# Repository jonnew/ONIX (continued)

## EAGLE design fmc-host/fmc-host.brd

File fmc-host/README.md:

:warning: This headstage has moved to a dedicated repository: https://github.com/open-ephys/onix-fmc-host.
This folder should be considered archived.

# FMC Host Board
This card serves as host interface for serialized headstages and miniscopes, as
well as general purpose analog and digital IO. This board is a VITA-57.1
compliant module that uses high pin-count FMC connector. In combination with a
base FPGA board (e.g. [Numato Lab
Nereid](https://numato.com/product/nereid-kintex-7-pci-express-fpga-development-board),
it provides host PC communication for the following:

- Two deserailizers for any multifunction headstage conforming to our
  serialization protocol
- 12x 16-bit, +/-10V analog outputs or inputs. Direction selected via analog
  switch controllable over the FMC connector. Analog inputs are separated into
  2 simultaneously sampled 6-channel banks. When analog outputs are used, they
  are are always looped back using the analog inputs.
- 3x high speed LVDS input pairs
- 2x high speed LVDS outputs pairs
- 2x high speed, arbitrary logic-level, singled-ended lock inputs
- 1x high speed single ended, 50 ohm clock output
- 4x MLVDS input or output trigger lines

Easy access to IO is provided by the [breakout board](../breakout/README.md).

## Gerber Files
{% include gerber_layers.md %}

## Bill of Materials
The bill of materials for this device can be found
[here](https://docs.google.com/spreadsheets/d/1F-KWcdvH_63iXjZf0cgCfDiFX6XXW3qw6rlR8DZrFpQ/edit#gid=1976092058).

## Manufacturing Requirements
In order to meet approximately correct trace impedances, the design assumes the following stackup:

1. Top Copper 0.035 mm
1. Prepreg (2313\*1) 0.1 mm
1. Inner Copper 0.0175 mm
1. Core (Copper) 0.565 mm
1. Inner Copper 0.0175 mm
1. Prepeg (2116\*1) 0.127 mm
1. Inner Copper 0.0175 mm
1. Core (Copper) 0.565 mm
1. Inner Copper 0.0175 mm
1. Prepreg (2313\*1) 0.1 mm
1. Bottom Copper 0.0175 mm

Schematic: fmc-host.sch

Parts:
C1, C2, C6, C7, C27, C28, C35, C36, C37, C38, C72, C73, C74, C75, C81, C82, C83, C93, C94, C108, C120, C139, C140: 10uF; 1206
C3, C4, C8, C9, C10, C11, C14, C15, C16, C17, C18, C19, C20, C23, C24, C31, C32, C33, C34, C39, C43, C45, C46, C47, C48, C49, C50, C51, C54, C55, C56, C57, C58, C62, C63, C65, C67, C69, C70, C80, C85, C86, C87, C88, C89, C91, C92, C95, C101, C102, C106, C109, C112, C113, C114, C116, C117, C133, C134, C135, C137, C138: 0.1uF; 0402
C5, C29, C30: 4.7nF; 0402
C12, C13, C21, C22, C25, C26, C52, C53, C59, C60, C84, C124, C125, C126: 10nF; 0402
C40, C41: 47nF; 0402
C42, C44, C66, C68, C76, C77, C78, C90: 1uF; 0805
C61, C64, C71, C79, C97, C98, C103, C105, C107, C110, C111, C115, C118, C119, C121, C122, C123, C127, C128, C129: 10uF; 0805
C96, C99, C100, C104, C130, C131, C132, C136: 47uF; 1210
D1, D2, D3: HSMG-C280; LED-0402
D4, D5: SESD0402X1UN-0020-090; 0402P-DFN
D6, D7, D8: BAR66; SOT23
D9: KDZ4.3B; SOD123
D10, D11: APFA3011-AK13/F; RGB_LED_SMD-6
F1, F2, F3: C014F-2; 1812
J1, J2, J3, J4, J5: SMA002; MMCX-THRU
J6: ESHF-105-01-L-D-SM-K-TR
J7: 12226-8250-00FR; 12226-82X0-00XX
J8: 95278-101A16LF; JP2X8_SMD
J9: FMC_SINGLE_WIDTH_MODULE
J10: ASP-134488-01; FMC_HPC_MALE
L1, L2: 1008PS-472; 1008PS
L3, L4, L9, L10, L11, L12: BLM18KG601SN1D; 0603
L5, L6: SRNxx-101M; SRN6045TA
L7, L8: MPZ2012S102AT000; 0805
L13: L_1210; 1210
L14, L15, L16, L17, L18, L19: BLM15PX601SN1D; 0402; PARTNO BLM15PX601SN1D
Q1, Q2: SI1012R; SC75
R1, R6, R7, R12, R13, R63, R64: 2k; 0402
R2, R3, R36, R37, R38, R39, R46, R49, R77, R79, R81: 4.7k; 0402
R4, R5, R33, R44, R45: 3k; 0402
R8, R9, R10, R11, R14, R15: 150,0.25W; 0603
R16, R17, R55, R56, R57, R58, R82: 165k; 0402
R18, R19, R41, R43, R65, R70, R71, R72, R73, R74, R84, R85: 10k; 0402
R20, R21, R47, R48, R50, R51, R52, R53: 1k; 0402
R22, R24: 5.6k 1%; 0402
R23, R25: 21k 1%; 0402
R26, R27: 60 1%; 0402
R28, R29, R34, R35: 49.9; 0402
R30, R31, R32: 100; 0402
R40, R42: DNP; 0402
R54, R69: 0; 0402
R59, R60, R61, R62: 2.2k; RN2X8-1506
R66, R67: 3.48k; 0402
R68: 649k; 0402
R75: 2.2k; 0402
R76: 15k; 0402
R78, R80: 43k; 0402
R83: 178k; 0402
R86, R87: 73.2k; 0402
S1, S2: CHS-01TA; DIP01-SMD-GULL
S3: CHS-02TB
SJ1, SJ2: SJ2_0201; SJ_2_0201
TP1, TP2, TP4, TP5, TP6, TP7, TP11, TP12, TP13, TP14, TP15, TP16: TPB1,27; B1,27
TP3, TP8, TP9, TP10, TP17, TP18: TPB2,54; B2,54
U1: SN74LVC2G34DCKR; SC70
U2: SN65LVDS9638DGN; MSOP-8-PAD-3X3
U3: FIN1032MTCX; TSSOP-16
U4: LTC2875_DFN; DFN83X3
U5, U6: ADCMP600; SOT-23-5
U7, U8, U9: DG1412E; QFN16-4X4MM
U10, U11: DS90UB934-Q1; WQFN48-7X7-PAD
U12: DS91M040; WQFN32-5X5
U13: AD5766BCPZ-RL7; CP_40_7
U14: MCP47FEB02A0-E/ST; TSSOP-8
U15: LM4132AMF-2.5/NOPBCT-ND; SOT-23-5
U16: AD7617BSTZ; ST_80_2
U17: AD5142BCPZ10; CP_16_27-L
U18: LTM4622A; BGA_5X5_625X625
U19: TPS62293DRV; WSON6-2X2
U20, U21: TPS7A49; PVSON-N8+4-3X3
U22: TPS7A30; PVSON-N8+4-3X3
U23: 24AA64ST; TSSOP8
U24: LTM8049_BGA; LTM8049
X2, X3: OE-LOGO_7X5; OE-LOGO-7X5

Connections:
!ADC_CS: J10.H13 (LA07_P), U16.63 (!CS)
!ADC_RESET: J10.F10 (HA08_P), R72.2
!DAC_CS: J10.J16 (HA14_N), U13.8 (!CS)
!DAC_RESET: J10.F14 (HA12_N), U13.3 (!RESET)
!LINK_PWR_ADJ_CS: J10.F38 (HB20_N), U17.14 (!CS)
!LINK_PWR_ADJ_RESET: J10.E37 (HB21_N), U17.16 (!RESET)
$N1: D8.3 (COMM), F2.2, R5.2, R9.2, R11.2, R15.2, R29.1
$N2: D6.3 (COMM), F3.2, U1.4 (OUT2), U1.6 (OUT1)
$N3: D7.3 (COMM), F1.2, R4.2, R8.2, R10.2, R14.2, R28.1
+1V8: C88.2, C89.2, C93.2, C94.2, C108.2, L3.2, L4.2, L9.1, L10.1, L13.1, R22.1, R24.1, R40.1, R42.1, TP16.TP, U10.17 (VDD18), U11.17 (VDD18), U19.3 (FB)
+3V3: C11.2, C23.1, C24.1, C29.1, C30.1, C33.1, C34.1, C39.1, C76.2, C80.2, C84.2, C91.2, C95.2, C98.2, C113.2, C115.2, C116.2, C119.2, C120.2, C136.2, C137.2, C138.2, C139.1, C140.1, J10.E39 (VADJ), J10.F40 (VADJ), J10.G39 (VADJ), J10.H40 (VADJ), J10.J39 (VIO_B_M2C), J10.K40 (VIO_B_M2C), L11.1, L12.1, R36.2, R37.2, R38.2, R39.2, R46.2, R49.2, R63.2, R64.2, R69.1, R70.1, R71.1, R75.1, R84.2, R85.2, S1.2, S2.2, TP11.TP, U1.5 (VCC), U2.1 (VCC), U3.4 (EN), U3.16 (VCC), U4.3 (VCC), U5.5 (V+), U6.5 (V+), U10.4 (OSS_SEL), U10.5 (OEN), U11.4 (OSS_SEL), U11.5 (OEN), U12.11 (VDD), U12.12 (VDD), U12.29 (VDD), U12.30 (VDD), U13.4 (VLOGIC), U14.1 (VDD), U14.2 (REFA), U16.49 (VDRIVE), U17.9 (VDD), U17.10 (VLOGIC), U17.15 (INDEP), U19.2 (MODE), U19.4 (EN), U19.5 (VIN), U24.A5 (VIN1), U24.A6 (VIN1), U24.A7 (VIN1), U24.B7 (RUN1), U24.K7 (RUN2), U24.L5 (VIN2), U24.L6 (VIN2), U24.L7 (VIN2)
+5V_AN: C61.2, C64.2, C71.2, C79.2, C83.1, C85.2, C86.2, C87.2, C92.2, C109.2, C110.2, L14.1, R1.2, TP1.TP, U13.28 (AVCC), U15.3 (EN), U15.4 (VIN), U16.6 (VCC), U16.15 (VCC), U16.30 (VCC), U16.71 (VCC)
+12V: C118.2, C130.2, C133.2, C134.2, J7.1, J7.26, J10.C35 (12P0V1), J10.C37 (12P0V2), R44.2, R45.2, TP12.TP, U18.A2 (VIN), U18.B3 (VIN), U18.D3 (VIN), U18.E2 (VIN)
+13V_AN: C8.2, C9.2, C10.2, C106.2, C107.2, L15.1, R2.2, TP2.TP, U7.11 (V+), U8.11 (V+), U9.11 (V+), U13.26 (AVDD)
+15V: C131.2, L17.2, L18.2, R82.1, U24.A1 (VOUT1P), U24.A2 (VOUT1P), U24.B1 (VOUT1P), U24.B2 (VOUT1P)
-13V_AN: C18.2, C19.2, C20.2, C101.2, C105.2, L16.1, R3.2, TP4.TP, U7.2 (V-), U7.PAD (V-), U8.2 (V-), U8.PAD (V-), U9.2 (V-), U9.PAD (V-), U13.6 (AVSS), U13.PAD (AVSS)
-15V: C132.1, L19.2, R83.1, U24.G1 (VOUT2N), U24.G2 (VOUT2N), U24.H1 (VOUT2N), U24.H2 (VOUT2N), U24.J2 (VOUT2N)
ADC_BUSY: J10.J12 (HA11_P), U16.67 (BUSY)
ADC_CONVST: J10.K13 (HA10_P), U16.68 (CONVST)
ADC_MISO_A: J10.K11 (HA06_N), U16.57 (DB12/SDOA)
ADC_MISO_B: J10.J10 (HA07_N), U16.56 (DB11/SDOB)
ADC_MOSI: J10.K10 (HA06_P), U16.55 (DB10/SDI)
ADC_SCLK: J10.J13 (HA11_N), U16.62 (SCLK/!RD)
ADDR0: J10.C27 (LA27_N), R84.1, S3.4
ADDR1: J10.C26 (LA27_P), R85.1, S3.3
AGND: C8.1, C9.1, C10.1, C18.1, C19.1, C20.1, C61.1, C64.1, C71.1, C79.1, C83.2, C85.1, C86.1, C87.1, C90.1, C92.1, C97.1, C101.1, C102.1, C103.1, C105.1, C106.1, C107.1, C109.1, C110.1, D1.C, D2.C, D3.A, J7.13, J7.14, R54.1, R59.C2, R59.C4, R59.C6, R59.C7, R60.C1, R60.C3, R60.C5, R60.C6, R60.C7, R60.C8, R61.C2, R61.C3, R61.C5, R61.C7, R62.C1, R62.C2, R62.C3, R62.C4, R62.C6, R62.C8, TP3.TP, U7.3 (GND), U8.3 (GND), U9.3 (GND), U13.10 (AGND), U13.20 (NIC), U13.23 (N0), U13.24 (N1), U13.25 (NIC), U13.29 (AGND), U13.31 (NIC), U15.2 (GND), U16.5 (AGND), U16.16 (AGND), U16.29 (AGND), U16.32 (REFGND), U16.34 (REFINOUTGND), U16.69 (REGGND), U16.72 (AGND)
AIN_AOUT0: J10.F11 (HA08_N), U9.15 (IN1)
AIN_AOUT1: J10.D11 (LA05_P), U9.6 (IN4)
AIN_AOUT2: J10.E12 (HA13_P), U9.7 (IN3)
AIN_AOUT3: J10.H10 (LA04_P), U9.14 (IN2)
AIN_AOUT4: J10.E18 (HA20_P), U8.15 (IN1)
AIN_AOUT5: J10.J9 (HA07_P), U8.6 (IN4)
AIN_AOUT6: J10.G10 (LA03_N), U8.7 (IN3)
AIN_AOUT7: J10.F17 (HA15_N), U8.14 (IN2)
AIN_AOUT8: J10.H20 (LA15_N), U7.7 (IN3)
AIN_AOUT9: J10.J18 (HA18_P), U7.14 (IN2)
AIN_AOUT10: J10.G19 (LA16_N), U7.6 (IN4)
AIN_AOUT11: J10.H19 (LA15_P), U7.15 (IN1)
AIO_0: J7.7, R59.C1, U9.16 (D1)
AIO_1: J7.20, R59.C3, U9.5 (D4)
AIO_2: J7.8, R59.C5, U9.8 (D3)
AIO_3: J7.21, R59.C8, U9.13 (D2)
AIO_4: J7.9, R60.C4, U8.16 (D1)
AIO_5: J7.22, R60.C2, U8.5 (D4)
AIO_6: J7.10, R62.C5, U8.8 (D3)
AIO_7: J7.23, R62.C7, U8.13 (D2)
AIO_8: J7.11, R61.C6, U7.8 (D3)
AIO_9: J7.24, R61.C8, U7.13 (D2)
AIO_10: J7.12, R61.C4, U7.5 (D4)
AIO_11: J7.25, R61.C1, U7.16 (D1)
AOUT0: U7.1 (S1), U13.32 (VOUT0)
AOUT1: U7.4 (S4), U13.33 (VOUT1)
AOUT2: U7.9 (S3), U13.34 (VOUT2)
AOUT3: U7.12 (S2), U13.35 (VOUT3)
AOUT4: U8.1 (S1), U13.36 (VOUT4)
AOUT5: U8.4 (S4), U13.37 (VOUT5)
AOUT6: U8.12 (S2), U13.38 (VOUT6)
AOUT7: U8.9 (S3), U13.39 (VOUT7)
AOUT8: U9.9 (S3), U13.12 (VOUT8)
AOUT9: U9.12 (S2), U13.13 (VOUT9)
AOUT10: U9.4 (S4), U13.14 (VOUT10)
AOUT11: U9.1 (S1), U13.15 (VOUT11)
CAN_N: R27.2, SJ1.2, U4.6 (CANL)
CAN_P: R26.2, SJ2.2, U4.7 (CANH)
CAN_RX: J10.K8 (HA02_N), U4.4 (RXD)
CAN_TX: J10.K7 (HA02_P), U4.1 (TXD)
CLKIN0: J10.D21 (LA17_N_CC), TP7.TP, U5.1 (OUT)
CLKIN1: J10.E19 (HA20_N), TP6.TP, U6.1 (OUT)
CLKIN_TERM0: J10.K19 (HA21_P), R20.1
CLKIN_TERM1: J10.K17 (HA17_N_CC), R21.1
CLKIN_VBIAS_SCL: J10.J21 (HA22_P), R64.1, U14.7 (SCL)
CLKIN_VBIAS_SDA: J10.K20 (HA21_N), R63.1, U14.8 (SDA)
CLKOUT: J10.D20 (LA17_P_CC), U1.1 (IN3), U1.3 (IN2)
DAC_MISO: J10.K16 (HA17_P_CC), U13.9 (MISO)
DAC_MOSI: J10.H14 (LA07_N), U13.5 (MOSI)
DAC_MUX: TP15.TP, U13.27 (MUX_OUT)
DAC_SCLK: J10.J15 (HA14_P), U13.7 (SCLK)
DEBUG0: J8.2, J10.C10 (LA06_P)
DEBUG1: J8.4, J10.C11 (LA06_N)
DEBUG2: J8.6, J10.D14 (LA09_P)
DEBUG3: J8.8, J10.C14 (LA10_P)
DEBUG4: J8.10, J10.D15 (LA09_N)
DEBUG5: J8.12, J10.C15 (LA10_N)
DEBUG6: J8.14, J10.C18 (LA14_P)
DEBUG7: J8.16, J10.C19 (LA14_N)
DES_A_D0: J10.F34 (HB16_P), U11.24 (ROUT0)
DES_A_D1: J10.K35 (HB14_N), U11.23 (ROUT1)
DES_A_D2: J10.J34 (HB15_N), U11.22 (ROUT2)
DES_A_D3: J10.K34 (HB14_P), U11.21 (ROUT3)
DES_A_D4: J10.E33 (HB19_P), U11.19 (ROUT4)
DES_A_D5: J10.J33 (HB15_P), U11.18 (ROUT5)
DES_A_D6: J10.F32 (HB12_N), U11.16 (ROUT6)
DES_A_D7: J10.E31 (HB13_N), U11.15 (ROUT7)
DES_A_D8: J10.K32 (HB10_N), U11.14 (ROUT8)
DES_A_D9: J10.F31 (HB12_P), U11.13 (ROUT9)
DES_A_D10: J10.J31 (HB11_N), U11.12 (ROUT10)
DES_A_D11: J10.K31 (HB10_P), U11.11 (ROUT11)
DES_A_GPIO0: J10.J37 (HB18_N), U11.28 (GPIO0)
DES_A_GPIO1: J10.K37 (HB17_P_CC), U11.27 (GPIO1)
DES_A_GPIO2: J10.J36 (HB18_P), U11.26 (GPIO2)
DES_A_GPIO3: J10.E34 (HB19_N), R49.1, U11.25 (GPIO3/INTB)
DES_A_HSYNC: J10.E30 (HB13_P), U11.10 (HSYNC)
DES_A_LEDG: J10.F28 (HB08_P), R53.2
DES_A_LOCK: J10.E27 (HB09_P), R48.2, R56.2, U11.48 (LOCK)
DES_A_PASS: J10.J28 (HB07_N), R51.2, R58.2, U11.47 (PASS)
DES_A_PCLK: J10.K28 (HB06_P_CC), U11.8 (PCLK)
DES_A_PDB: J10.F35 (HB16_N), U11.30 (PDB)
DES_A_SCL: J10.F29 (HB08_N), R37.1, U11.2 (SCL)
DES_A_SDA\: J10.E28 (HB09_N), R39.1, U11.1 (SDA)
DES_A_VSYNC: J10.J30 (HB11_P), U11.9 (VSYNC)
DES_B_D0: J10.H29 (LA24_N), U10.24 (ROUT0)
DES_B_D1: J10.H28 (LA24_P), U10.23 (ROUT1)
DES_B_D2: J10.G28 (LA25_N), U10.22 (ROUT2)
DES_B_D3: J10.G27 (LA25_P), U10.21 (ROUT3)
DES_B_D4: J10.D27 (LA26_N), U10.19 (ROUT4)
DES_B_D5: J10.D26 (LA26_P), U10.18 (ROUT5)
DES_B_D6: J10.H26 (LA21_N), U10.16 (ROUT6)
DES_B_D7: J10.G25 (LA22_N), U10.15 (ROUT7)
DES_B_D8: J10.H25 (LA21_P), U10.14 (ROUT8)
DES_B_D9: J10.D24 (LA23_N), U10.13 (ROUT9)
DES_B_D10: J10.G24 (LA22_P), U10.12 (ROUT10)
DES_B_D11: J10.D23 (LA23_P), U10.11 (ROUT11)
DES_B_GPIO0: J10.H32 (LA28_N), U10.28 (GPIO0)
DES_B_GPIO1: J10.G31 (LA29_N), U10.27 (GPIO1)
DES_B_GPIO2: J10.H31 (LA28_P), U10.26 (GPIO2)
DES_B_GPIO3: J10.G30 (LA29_P), R46.1, U10.25 (GPIO3/INTB)
DES_B_HSYNC\: J10.H23 (LA19_N), U10.10 (HSYNC)
DES_B_LEDG: J10.G21 (LA20_P), R52.2
DES_B_LOCK: J10.J22 (HA22_N), R47.2, R55.2, U10.48 (LOCK)
DES_B_PASS: J10.K22 (HA23_P), R50.2, R57.2, U10.47 (PASS)
DES_B_PCLK: J10.C22 (LA18_P_CC), U10.8 (PCLK)
DES_B_PDB: J10.G33 (LA31_P), U10.30 (PDB)
DES_B_SCL: J10.G22 (LA20_N), R36.1, U10.2 (SCL)
DES_B_SDA: J10.H22 (LA19_P), R38.1, U10.1 (SDA)
DES_B_VSYNC: J10.K23 (HA23_N), U10.9 (VSYNC)
DI_VBIAS0: R18.1, U14.3 (VOUT0)
DI_VBIAS1: R19.1, U14.4 (VOUT1)
DOUTP_F_A: C47.2, D5.C, J2.SIG (1), L2.2, R7.2
DOUTP_F_B: C46.2, D4.C, J1.SIG (1), L1.2, R6.2
GND: C1.1, C2.1, C3.1, C4.1, C5.2, C6.1, C7.1, C11.1, C12.1, C13.1, C14.2, C15.2, C16.2, C17.2, C21.1, C22.1, C23.2, C24.2, C25.1, C26.1, C27.1, C28.1, C29.2, C30.2, C31.2, C32.2, C33.2, C34.2, C35.1, C36.1, C37.1, C38.1, C39.2, C42.1, C43.1, C44.1, C45.1, C48.1, C49.1, C50.1, C51.1, C52.1, C53.1, C54.1, C55.1, C56.1, C57.1, C58.1, C59.1, C60.1, C62.1, C63.1, C65.1, C66.1, C67.1, C68.1, C69.1, C70.1, C72.1, C73.1, C74.1, C75.1, C76.1, C77.1, C78.1, C80.1, C81.1, C82.1, C84.1, C88.1, C89.1, C91.1, C93.1, C94.1, C95.1, C96.1, C98.1, C99.1, C100.1, C104.1, C108.1, C111.1, C112.1, C113.1, C114.1, C115.1, C116.1, C117.2, C118.1, C119.1, C120.1, C121.1, C122.1, C123.1, C124.2, C125.2, C126.2, C127.1, C128.1, C129.1, C130.1, C131.1, C132.2, C133.1, C134.1, C135.1, C136.1, C137.1, C138.1, C139.2, C140.2, D4.A, D5.A, D6.1 (A), D7.1 (A), D8.1 (A), D9.A, D10.3 (C), D10.5 (C), D10.6 (C), D11.3 (C), D11.5 (C), D11.6 (C), J1.GND@1 (2), J1.GND@2 (2), J1.GND@3 (2), J1.GND@4 (2), J2.GND@1 (2), J2.GND@2 (2), J2.GND@3 (2), J2.GND@4 (2), J3.GND@1 (2), J3.GND@2 (2), J3.GND@3 (2), J3.GND@4 (2), J4.GND@1 (2), J4.GND@2 (2), J4.GND@3 (2), J4.GND@4 (2), J5.GND@1 (2), J5.GND@2 (2), J5.GND@3 (2), J5.GND@4 (2), J7.PAD1, J7.PAD2, J8.1, J8.3, J8.5, J8.7, J8.9, J8.11, J8.13, J8.15, J10.A1 (GND), J10.A4 (GND), J10.A5 (GND), J10.A8 (GND), J10.A9 (GND), J10.A12 (GND), J10.A13 (GND), J10.A16 (GND), J10.A17 (GND), J10.A20 (GND), J10.A21 (GND), J10.A24 (GND), J10.A25 (GND), J10.A28 (GND), J10.A29 (GND), J10.A32 (GND), J10.A33 (GND), J10.A36 (GND), J10.A37 (GND), J10.A40 (GND), J10.B2 (GND), J10.B3 (GND), J10.B6 (GND), J10.B7 (GND), J10.B10 (GND), J10.B11 (GND), J10.B14 (GND), J10.B15 (GND), J10.B18 (GND), J10.B19 (GND), J10.B22 (GND), J10.B23 (GND), J10.B26 (GND), J10.B27 (GND), J10.B30 (GND), J10.B31 (GND), J10.B34 (GND), J10.B35 (GND), J10.B38 (GND), J10.B39 (GND), J10.C1 (GND), J10.C4 (GND), J10.C5 (GND), J10.C8 (GND), J10.C9 (GND), J10.C12 (GND), J10.C13 (GND), J10.C16 (GND), J10.C17 (GND), J10.C20 (GND), J10.C21 (GND), J10.C24 (GND), J10.C25 (GND), J10.C28 (GND), J10.C29 (GND), J10.C32 (GND), J10.C33 (GND), J10.C34 (GA0), J10.C36 (GND), J10.C38 (GND), J10.C40 (GND), J10.D2 (GND), J10.D3 (GND), J10.D6 (GND), J10.D7 (GND), J10.D10 (GND), J10.D13 (GND), J10.D16 (GND), J10.D19 (GND), J10.D22 (GND), J10.D25 (GND), J10.D28 (GND), J10.D35 (GA1), J10.D37 (GND), J10.D39 (GND), J10.E1 (GND), J10.E4 (GND), J10.E5 (GND), J10.E8 (GND), J10.E11 (GND), J10.E14 (GND), J10.E17 (GND), J10.E20 (GND), J10.E23 (GND), J10.E26 (GND), J10.E29 (GND), J10.E32 (GND), J10.E35 (GND), J10.E38 (GND), J10.E40 (GND), J10.F2 (GND), J10.F3 (GND), J10.F6 (GND), J10.F9 (GND), J10.F12 (GND), J10.F15 (GND), J10.F18 (GND), J10.F21 (GND), J10.F24 (GND), J10.F27 (GND), J10.F30 (GND), J10.F33 (GND), J10.F36 (GND), J10.F39 (GND), J10.G1 (GND), J10.G4 (GND), J10.G5 (GND), J10.G8 (GND), J10.G11 (GND), J10.G14 (GND), J10.G17 (GND), J10.G20 (GND), J10.G23 (GND), J10.G26 (GND), J10.G29 (GND), J10.G32 (GND), J10.G35 (GND), J10.G38 (GND), J10.G40 (GND), J10.H3 (GND), J10.H6 (GND), J10.H9 (GND), J10.H12 (GND), J10.H15 (GND), J10.H18 (GND), J10.H21 (GND), J10.H24 (GND), J10.H27 (GND), J10.H30 (GND), J10.H33 (GND), J10.H36 (GND), J10.H39 (GND), J10.J1 (GND), J10.J4 (GND), J10.J5 (GND), J10.J8 (GND), J10.J11 (GND), J10.J14 (GND), J10.J17 (GND), J10.J20 (GND), J10.J23 (GND), J10.J26 (GND), J10.J29 (GND), J10.J32 (GND), J10.J35 (GND), J10.J38 (GND), J10.J40 (GND), J10.K2 (GND), J10.K3 (GND), J10.K6 (GND), J10.K9 (GND), J10.K12 (GND), J10.K15 (GND), J10.K18 (GND), J10.K21 (GND), J10.K24 (GND), J10.K27 (GND), J10.K30 (GND), J10.K33 (GND), J10.K36 (GND), J10.K39 (GND), Q1.2 (S), Q2.2 (S), R4.1, R5.1, R16.1, R17.1, R23.2, R25.2, R33.1, R34.2, R35.2, R41.2, R43.2, R54.2, R55.1, R56.1, R57.1, R58.1, R68.2, R73.2, R74.2, R77.1, R79.1, R81.1, R86.2, R87.2, S3.1, S3.2, TP8.TP, TP9.TP, TP10.TP, TP17.TP, TP18.TP, U1.2 (GND), U2.4 (GND), U2.PAD (GND), U3.8 (GND), U3.12 (!EN), U4.2 (GND), U4.PAD (GND), U5.2 (V-), U6.2 (V-), U10.43 (RES1), U10.44 (RES2), U10.46 (SEL), U10.PAD (GND), U11.43 (RES1), U11.44 (RES2), U11.46 (SEL), U11.PAD (GND), U12.31 (GND), U12.PAD (GND), U13.2 (DGND), U14.5 (AVSS), U14.6 (LAT/HVC), U16.37 (SEQEN), U16.38 (HW_RNGSEL1), U16.39 (HW_RNGSEL0), U16.41 (DB0), U16.42 (DB1), U16.43 (DB2), U16.44 (DB3), U16.46 (DB5/CRCEN), U16.47 (DB6), U16.48 (DB7), U16.50 (DGND), U16.51 (REGGNDD), U16.53 (DB8), U16.54 (DB9), U16.58 (DB13/OS0), U16.59 (DB14/OS1), U16.60 (DB15/OS2), U16.61 (WR!/BURST), U16.64 (CHSEL0), U16.65 (CHSEL1), U16.66 (CHSEL2), U17.1 (GND), U17.3 (W1), U17.5 (VSS), U17.7 (W2), U17.PAD (VSS), U18.B5 (GND), U18.C1 (GND), U18.C2 (GND), U18.C5 (SYNC/MODE), U18.D5 (GND), U19.6 (GND), U19.PAD (GND), U20.3 (NC), U20.4 (GND), U20.PAD1 (PAD), U20.PAD2 (PAD), U20.PAD3 (PAD), U20.PAD4 (PAD), U20.PAD5 (PAD), U21.3 (NC), U21.4 (GND), U21.PAD1 (PAD), U21.PAD2 (PAD), U21.PAD3 (PAD), U21.PAD4 (PAD), U21.PAD5 (PAD), U22.3 (NC), U22.4 (GND), U22.PAD1 (PAD), U22.PAD2 (PAD), U22.PAD3 (PAD), U22.PAD4 (PAD), U22.PAD5 (PAD), U23.1 (A0), U23.2 (A1), U23.3 (A2), U23.4 (GND), U23.7 (WP), U24.A3 (GND), U24.A4 (GND), U24.B3 (GND), U24.B4 (GND), U24.B5 (GND), U24.B6 (GND), U24.C2 (VOUT1N), U24.C3 (GND), U24.C4 (GND), U24.C5 (GND), U24.C6 (GND), U24.D1 (VOUT1N), U24.D2 (VOUT1N), U24.D3 (GND), U24.D4 (GND), U24.D5 (GND), U24.D7 (SYNC1), U24.E1 (VOUT1N), U24.E2 (VOUT1N), U24.E3 (GND), U24.E4 (GND), U24.E5 (GND), U24.F1 (GND), U24.F2 (GND), U24.F5 (GND), U24.F6 (GND), U24.F7 (GND), U24.G3 (GND), U24.G4 (GND), U24.G5 (GND), U24.H3 (GND), U24.H4 (GND), U24.H5 (GND), U24.J3 (GND), U24.J4 (GND), U24.J5 (GND), U24.J6 (GND), U24.K1 (VOUT2P), U24.K2 (VOUT2P), U24.K3 (GND), U24.K4 (GND), U24.K5 (GND), U24.K6 (GND), U24.L1 (VOUT2P), U24.L2 (VOUT2P), U24.L3 (GND), U24.L4 (GND)
LINK_A_PWR_EN: J10.H37 (LA32_P), R74.1, U18.B2 (RUN2)
LINK_B_PWR_EN: J10.K38 (HB17_N_CC), R73.1, U18.D2 (RUN1)
LINK_PWR_ADJ_MISO: J10.F37 (HB20_P), R75.2, U17.13 (MISO)
LINK_PWR_ADJ_MOSI: J10.E36 (HB21_P), U17.12 (MOSI)
LINK_PWR_ADJ_SCLK: J10.H38 (LA32_N), U17.11 (SCLK)
LVDS_DIN0: J10.J2 (CLK1_C2M_P), U3.3 (AOUT)
LVDS_DIN0_N: J7.4, R30.1, U3.1 (A-)
LVDS_DIN0_P: J7.17, R30.2, U3.2 (A+)
LVDS_DIN1: J10.H5 (CLK0_M2C_N), U3.5 (BOUT)
LVDS_DIN1_N: J7.16, R31.1, U3.7 (B-)
LVDS_DIN1_P: J7.3, R31.2, U3.6 (B+)
LVDS_DIN2: J10.H4 (CLK0_M2C_P), U3.11 (COUT)
LVDS_DIN2_N: R32.1, SJ2.1, U3.9 (C-)
LVDS_DIN2_N/CAN_P: J7.2, SJ2.COM
LVDS_DIN2_P: R32.2, SJ1.1, U3.10 (C+)
LVDS_DIN2_P/CAN_N: J7.15, SJ1.COM
LVDS_DOUT0: J10.J3 (CLK1_C2M_N), U2.2 (AIN)
LVDS_DOUT0_N: J7.19, U2.7 (AOUT-)
LVDS_DOUT0_P: J7.6, U2.8 (AOUT+)
LVDS_DOUT1: J10.K4 (CLK1_M2C_P), U2.3 (BIN)
LVDS_DOUT1_N: J7.18, U2.5 (BOUT-)
LVDS_DOUT1_P: J7.5, U2.6 (BOUT+)
MLDVS_EN: J10.H8 (LA02_N), U12.10 (MDE)
MLDVS_RO0: J10.G2 (CLK0_C2M_P), U12.1 (RO0)
MLDVS_RO1: J10.E3 (HA01_N_CC), U12.3 (RO1)
MLDVS_RO2: J10.G7 (LA00_N_CC), U12.5 (RO2)
MLDVS_RO3: J10.F4 (HA00_P_CC), U12.7 (RO3)
MLVDS_CLK_0_N: J6.9, U12.24 (B0)
MLVDS_CLK_0_P: J6.10, U12.23 (A0)
MLVDS_CLK_1_N: J6.7, U12.22 (B1)
MLVDS_CLK_1_P: J6.8, U12.21 (A1)
MLVDS_CLK_2_N: J6.3, U12.20 (B2)
MLVDS_CLK_2_P: J6.4, U12.19 (A2)
MLVDS_CLK_3_N: J6.1, U12.18 (B3)
MLVDS_CLK_3_P: J6.2, U12.17 (A3)
MLVDS_DE_!RE0: J10.F7 (HA04_P), U12.25 (DE0), U12.26 (!RE0)
MLVDS_DE_!RE1: J10.E7 (HA05_N), U12.27 (DE1), U12.28 (!RE1)
MLVDS_DE_!RE2: J10.H7 (LA02_P), U12.13 (!RE2), U12.14 (DE2)
MLVDS_DE_!RE3: J10.F8 (HA04_N), U12.15 (!RE3), U12.16 (DE3)
MLVDS_DI0: J10.G3 (CLK0_C2M_N), U12.2 (DI0)
MLVDS_DI1: J10.E2 (HA01_P_CC), U12.4 (DI1)
MLVDS_DI2: J10.G6 (LA00_P_CC), U12.6 (DI2)
MLVDS_DI3: J10.F5 (HA00_N_CC), U12.8 (DI3)
unnamed: L13.2, U19.1 (SW)
unnamed: Q1.3 (D), R8.1, R10.1, R14.1
unnamed: R28.2, U5.3 (+IN)
unnamed: L1.1, L5.2, R6.1, R12.2
unnamed: R67.1, U18.A4 (FB2)
unnamed: F2.1, J4.SIG (1)
unnamed: Q2.3 (D), R9.1, R11.1, R15.1
unnamed: C112.2, U18.A3 (TRACK/SS2)
unnamed: R87.1, U24.G7 (RT2)
unnamed: R66.1, U18.E4 (FB1)
unnamed: F1.1, J3.SIG (1)
unnamed: C114.2, U18.E3 (TRACK/SS1)
unnamed: R33.2, U4.8 (RS)
unnamed: F3.1, J5.SIG (1)
unnamed: C127.2, L17.1, U20.5 (EN), U20.8 (IN)
unnamed: D11.4 (A), R53.1
unnamed: R86.1, U24.E7 (RT1)
unnamed: C14.1, R18.2, U5.4 (-IN)
unnamed: R29.2, U6.3 (+IN)
unnamed: C15.1, R19.2, U6.4 (-IN)
unnamed: L2.1, L6.2, R7.1, R13.2
unnamed: C7.2, C17.1, L6.1, L8.2, R13.1
unnamed: R61.1, U16.79 (V3B)
unnamed: C6.2, C16.1, L5.1, L7.2, R12.1
unnamed: R83.2, U24.J1 (FBX2)
unnamed: D10.4 (A), R52.1
unnamed: C47.1, U11.41 (RIN0+)
unnamed: C41.1, U11.42 (RIN0-)
unnamed: R82.2, U24.C1 (FBX1)
unnamed: C37.2, C44.2, C49.2, U11.3 (VDD11_D)
unnamed: C38.2, C45.2, U11.20 (VDD11_DVP)
unnamed: C41.2, R35.1
unnamed: C124.1, U20.6 (NR/SS)
unnamed: Q2.1 (G), R17.2, R21.2
unnamed: U24.E6 (CLKOUT1), U24.H7 (SYNC2)
unnamed: D3.C, R3.1
unnamed: Q1.1 (G), R16.2, R20.2
unnamed: C46.1, U10.41 (RIN0+)
unnamed: R61.2, U16.80 (V3BGND)
unnamed: R76.1, R77.2, U20.2 (FB)
unnamed: C5.1, R26.1, R27.1, U4.5 (SPLIT)
unnamed: C128.2, L18.1, U21.5 (EN), U21.8 (IN)
unnamed: C125.1, U21.6 (NR/SS)
unnamed: C70.2, C78.2, C82.2, U11.34 (VDD11_FPD)
unnamed: C117.1, R72.1, U16.36 (!RESET)
unnamed: C57.2, C62.2, C66.2, C73.2, L11.2, U10.7 (VDDIO), U10.29 (VDDIO)
unnamed: C35.2, C42.2, C48.2, U10.3 (VDD11_D)
unnamed: C36.2, C43.2, U10.20 (VDD11_DVP)
unnamed: C69.2, C77.2, C81.2, U10.34 (VDD11_FPD)
unnamed: D11.1 (A), R48.1
unnamed: D11.2 (A), R51.1
unnamed: C40.1, U10.42 (RIN0-)
unnamed: R78.1, R79.2, U21.2 (FB)
unnamed: D1.A, R1.1
unnamed: C129.2, L19.1, U22.5 (EN), U22.8 (IN)
unnamed: C126.1, U22.6 (NR/SS)
unnamed: R80.1, R81.2, U22.2 (FB)
unnamed: R71.2, U16.45 (DB4/!SER1WR)
unnamed: R59.1, U16.28 (V0A)
unnamed: R70.2, U16.40 (SER/!PAR)
unnamed: C97.2, U16.31 (REFCAP)
unnamed: R59.2, U16.27 (V0AGND)
unnamed: D2.A, R2.1
unnamed: C111.2, U16.52 (REGCAPD)
unnamed: R61.8, U16.73 (V0B)
unnamed: C103.2, U16.70 (REGCAP)
unnamed: R69.2, U16.35 (REFSEL)
unnamed: R62.7, U16.2 (V4B)
unnamed: R62.1, U16.10 (V7BGND)
unnamed: R61.7, U16.74 (V0BGND)
unnamed: R61.6, U16.75 (V1B)
unnamed: R61.5, U16.76 (V1BGND)
unnamed: R61.4, U16.77 (V2B)
unnamed: R61.3, U16.78 (V2BGND)
unnamed: R59.3, U16.26 (V1A)
unnamed: R59.4, U16.25 (V1AGND)
unnamed: R59.5, U16.24 (V2A)
unnamed: R59.6, U16.23 (V2AGND)
unnamed: R59.8, U16.22 (V3A)
unnamed: R59.7, U16.21 (V3AGND)
unnamed: R60.2, U16.19 (V4A)
unnamed: R60.1, U16.20 (V4AGND)
unnamed: R60.4, U16.17 (V5A)
unnamed: R60.3, U16.18 (V5AGND)
unnamed: R60.5, U16.14 (V6A)
unnamed: R60.6, U16.13 (V6AGND)
unnamed: R60.7, U16.12 (V7A)
unnamed: R60.8, U16.11 (V7AGND)
unnamed: C40.2, R34.1
unnamed: R62.8, U16.1 (V4BGND)
unnamed: R62.5, U16.4 (V5B)
unnamed: R62.6, U16.3 (V5BGND)
unnamed: R62.4, U16.7 (V6B)
unnamed: R62.3, U16.8 (V6BGND)
unnamed: R62.2, U16.9 (V7B)
unnamed: R40.2, R41.1, U10.35 (IDX)
unnamed: D10.1 (A), R47.1
unnamed: D10.2 (A), R50.1
unnamed: R66.2, U17.2 (A1)
unnamed: R67.2, U17.6 (A2)
unnamed: R68.1, U18.C4 (FREQ)
unnamed: C58.2, C63.2, C68.2, C75.2, L12.2, U11.7 (VDDIO), U11.29 (VDDIO)
unnamed: S2.1, U11.6 (BISTEN)
unnamed: R24.2, R25.1, U11.37 (MODE)
unnamed: R42.2, R43.1, U11.35 (IDX)
unnamed: C121.2, L14.2, R76.2, U20.1 (OUT)
unnamed: C122.2, L15.2, R78.2, U21.1 (OUT)
unnamed: C123.2, L16.2, R80.2, U22.1 (OUT)
unnamed: C102.2, R65.1, U16.33 (REFINOUT)
unnamed: S1.1, U10.6 (BISTEN)
unnamed: R22.2, R23.1, U10.37 (MODE)
SCL: J10.C30 (SCL), U23.6 (SCL)
SDA: J10.C31 (SDA), U23.5 (SDA)
TDI-TDO: J10.D30 (TDI), J10.D31 (TDO)
VAUX: C135.2, J10.D32 (3P3VAUX), U23.8 (VCC)
VDD_FPDX_A: C2.2, C4.2, C13.2, C22.2, C26.2, L4.1, U11.31 (VDD18_FPD1), U11.40 (VDD18_FPD0)
VDD_FPDX_B: C1.2, C3.2, C12.2, C21.2, C25.2, L3.1, U10.31 (VDD18_FPD1), U10.40 (VDD18_FPD0)
VDD_PX_A: C51.2, C53.2, C56.2, C60.2, C67.2, C74.2, L10.2, U11.36 (VDD18_P1), U11.45 (VDD18_P0)
VDD_PX_B: C50.2, C52.2, C55.2, C59.2, C65.2, C72.2, L9.2, U10.36 (VDD18_P1), U10.45 (VDD18_P0)
VLINK_A: C28.2, C32.1, C96.2, C99.2, L8.1, TP13.TP, U18.A1 (VOUT2), U18.B1 (VOUT2)
VLINK_B: C27.2, C31.1, C100.2, C104.2, L7.1, TP14.TP, U18.D1 (VOUT1), U18.E1 (VOUT1)
VREF: C90.2, R65.2, U13.22 (VREF), U15.5 (VOUT)
V_PROTECT: C54.2, D6.2 (C), D7.2 (C), D8.2 (C), D9.C, R44.1, R45.1, TP5.TP

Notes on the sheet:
FMC
NB: Input protection voltage ~4.6V
L2 is the smallest package size I could find that barely meets current saturation requriements. An 8x8mm device that is probably safer is the Bourns SRN8040TA series.
Power: ~1.3A DC at 12V; 15.6W. With 90% efficiency regulation to 5.5V at serializer, this translates to 2.55A available, which is enough for 1A/LED + 500 mA serializer and FPGA.
DNP
NB: Use both MISO lines
NB: R-arrays provide input protection. Limit current thru internal clamp diodes to 10 mA at 20V.
NB: Worst case 100 mA draw from both ADC and DAC. With 10V stepdown, this is 1W dissipation.
ANALOG IO
CLK/TRIGGER I/0
NB: 3.48k = 11V output.
NB: VADJ must be set to 1.8V on host board!
NB: GA0 and GA1 define the LSBs of the EEPROM I2C address. We use 0x1010000
NB: FMC FRU module. Required by FMC standard.
Quad 1
Quad 2
Quad 3
NB: For best performance, quads should only be input or output, not mixtures.
TP1
TP2
TP3
TP4
TP5
NB: VLINK adjust. - Max step down ratio: 1 - (45e-9 *1.48e6) = 0.933 - So max voltage = 11.19 - Linear mode selected - R_AW = 0 : VLINK = 11.0V - R_AW = 5k : VLINK = 5.0V - General: VLINK = 36.24k/(3.48k + R_AW) + 0.6
NB: Default VBIAS = 1.65V
LINK A
LINK POWER
ANALOG POWER
LINK B
CLK IN 0
CLK IN 1
CLK OUT
FMC IO
HPC FMC
INTERNAL CLK/TRIG
SYNC
NB: Board address
NB: P,N order matches SDR datasheet spec.
NB: DC signals so no worries about DGND
NB: TO CC Pin

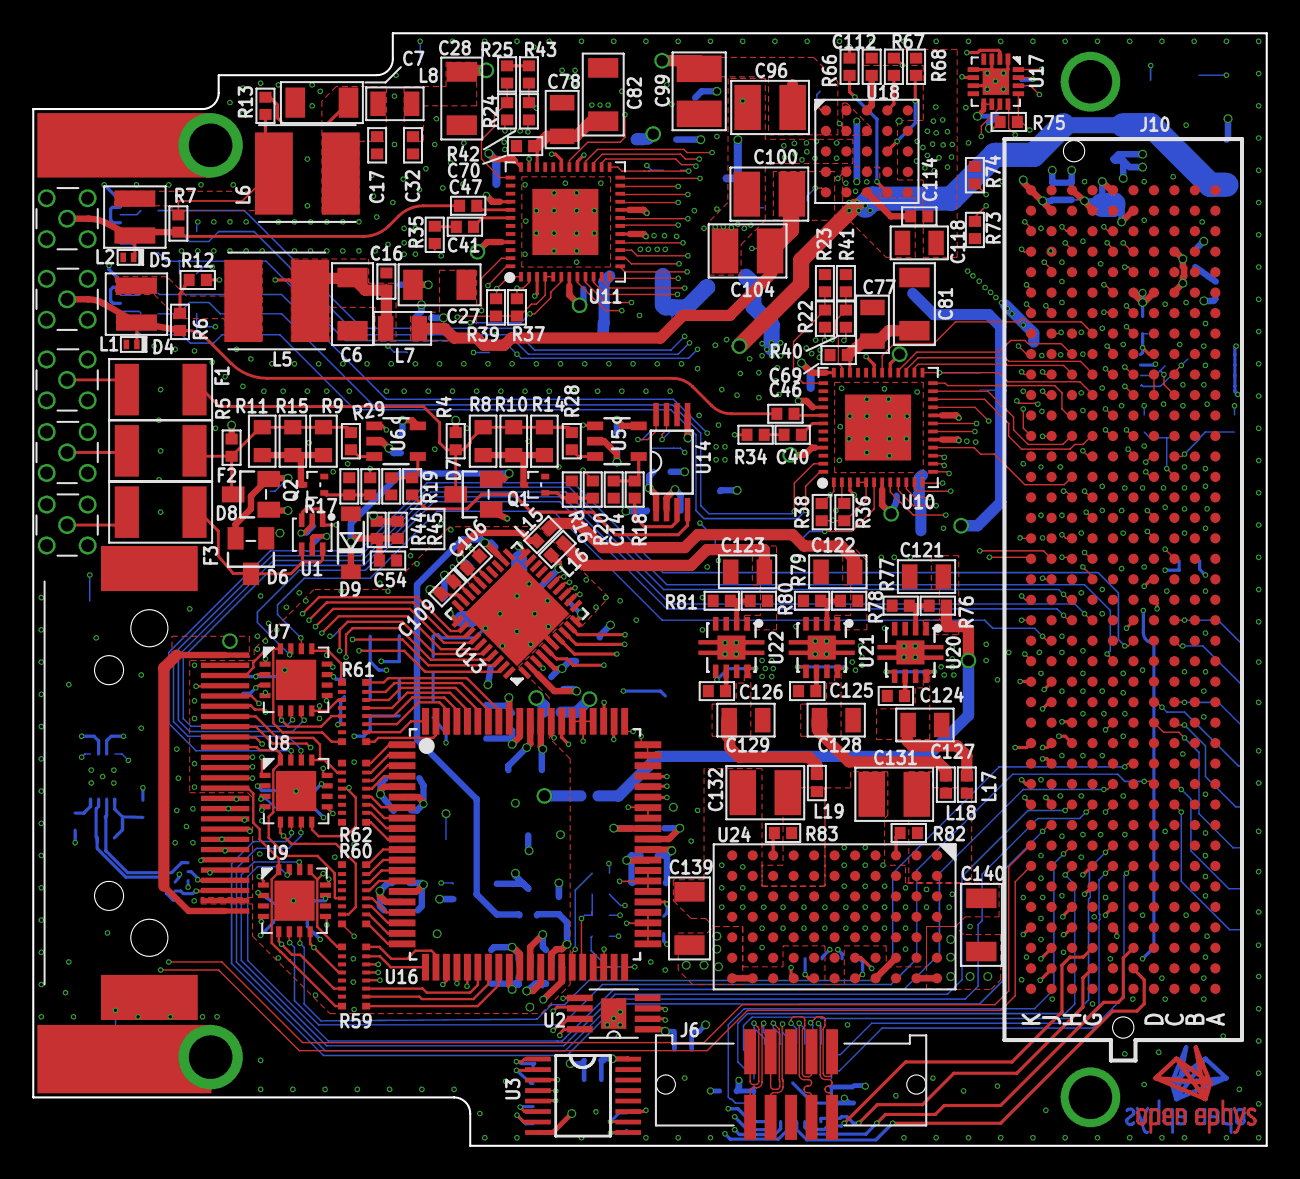
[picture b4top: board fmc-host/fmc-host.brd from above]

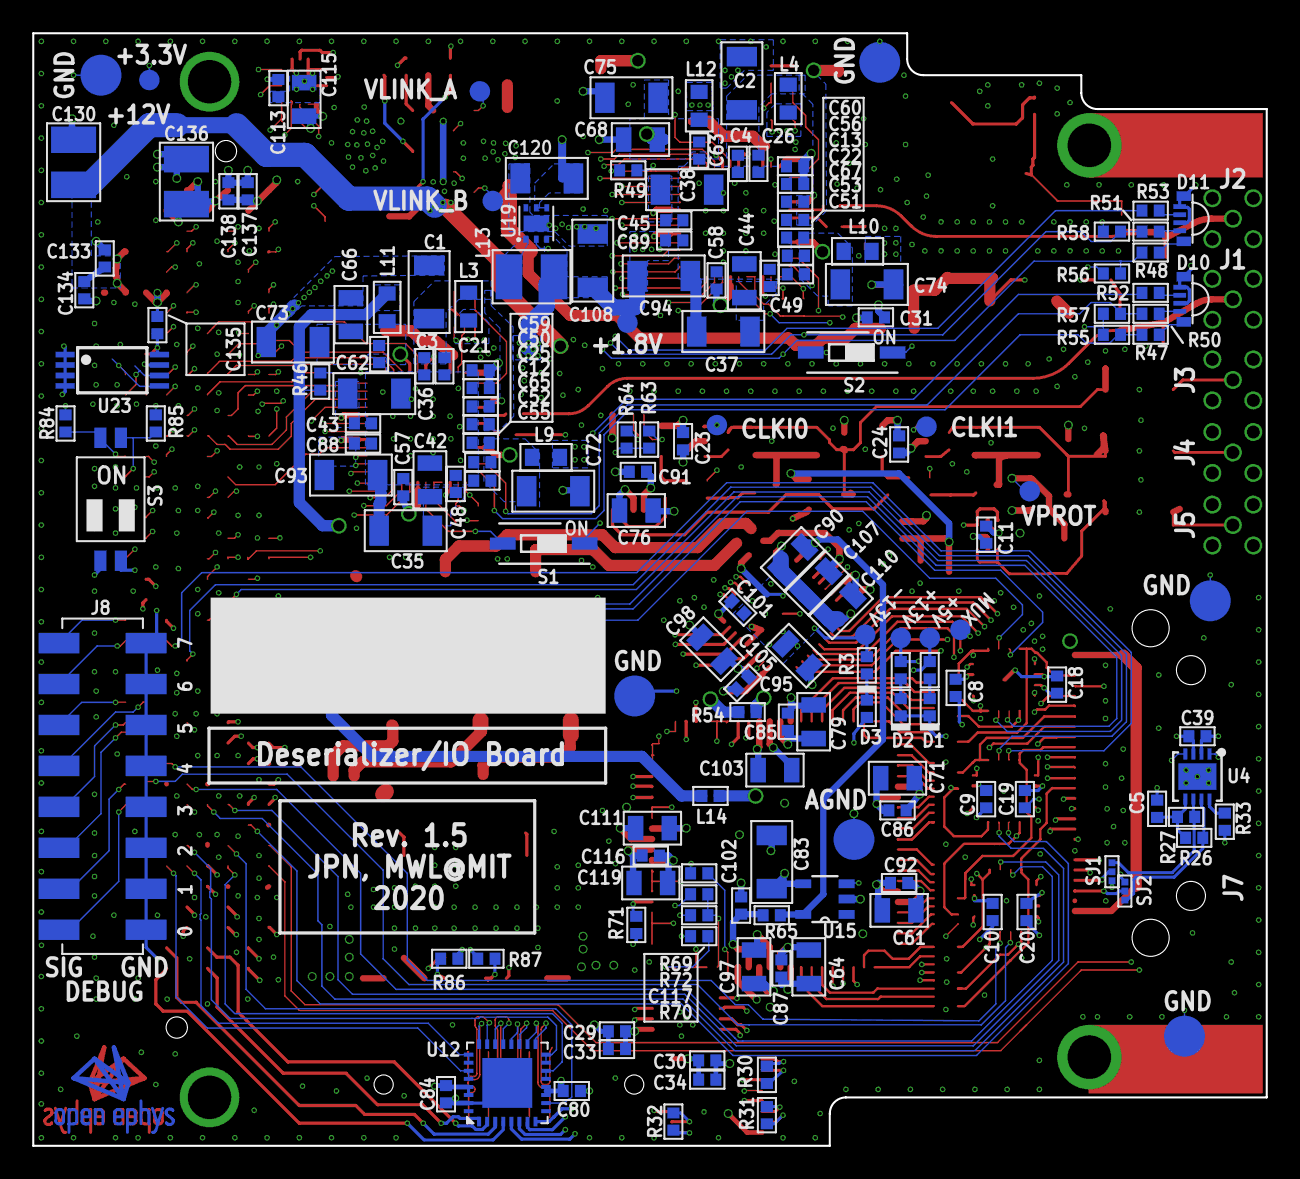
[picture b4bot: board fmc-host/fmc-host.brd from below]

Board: 6 copper layers, 76.5 x 69.0 mm, 321 parts (174 on the bottom side), 306 nets.
